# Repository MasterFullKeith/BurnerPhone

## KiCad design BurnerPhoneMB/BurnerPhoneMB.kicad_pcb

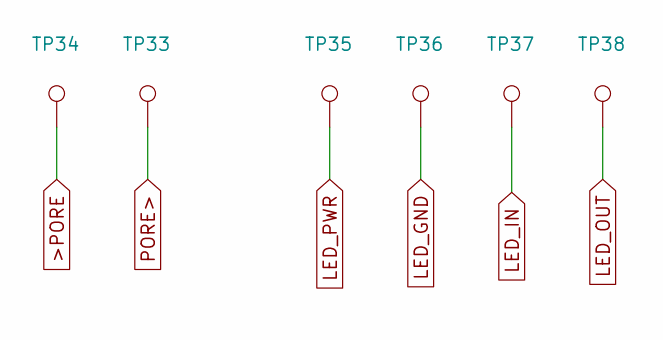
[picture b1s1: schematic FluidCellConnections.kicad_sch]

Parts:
TP33, TP34, TP35, TP36, TP37, TP38: TestPoint; Test Point

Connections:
>PORE: TP34.1; also elsewhere on the board
LED_GND: TP36.1
LED_IN: TP37.1
LED_OUT: TP38.1
LED_PWR: TP35.1
PORE>: TP33.1; also elsewhere on the board

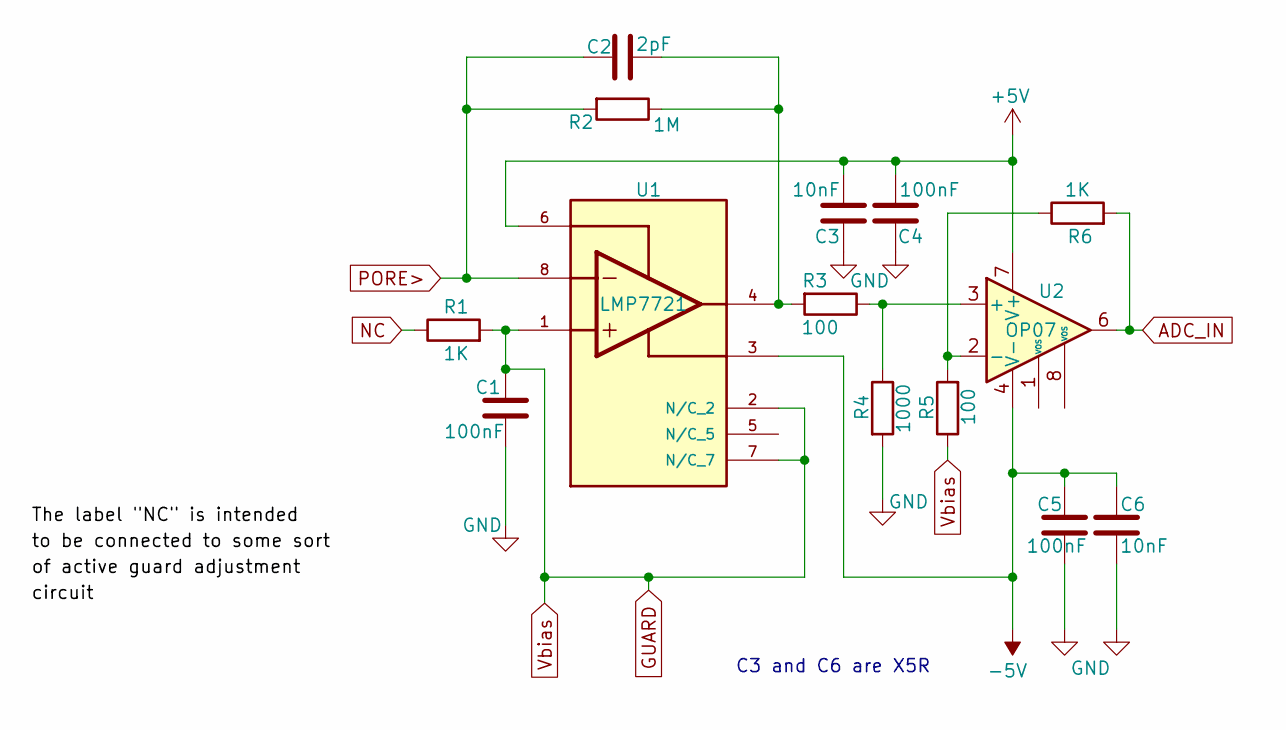
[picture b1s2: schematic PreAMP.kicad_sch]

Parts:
C1, C4, C5: 100nF; R_0805_2012Metric
C2: 2pF; R_0805_2012Metric
C3, C6: 10nF; R_0805_2012Metric
R1, R6: 1K; R_0805_2012Metric
R2: 1M; R_0805_2012Metric
R3, R5: 100; R_0805_2012Metric
R4: 1000; R_0805_2012Metric
U1: LMP7721; SOIC-8-1EP_3.9x4.9mm_P1.27mm_EP2.29x3mm; PARTREV E
U2: OP07; SOIC-8-1EP_3.9x4.9mm_P1.27mm_EP2.29x3mm

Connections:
+5V: C3.2, C4.2, U1.6, U2.7 (V+); also elsewhere on the board
-5V: C5.1, C6.1, U1.3, U2.4 (V-); also elsewhere on the board
ADC_IN: R6.2, U2.6; also elsewhere on the board
GND: C1.2, C3.1, C4.1, C5.2, C6.2, R4.2; also elsewhere on the board
GUARD: C1.1, R1.2, R5.1, U1.1, U1.2 (N/C), U1.7 (N/C)
NC: R1.1
unnamed: C2.1, R2.1, R3.2, U1.4
unnamed: R3.1, R4.1, U2.3 (+)
unnamed: R5.2, R6.1, U2.2 (-)
PORE>: C2.2, R2.2, U1.8; also elsewhere on the board

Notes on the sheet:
C3 and C6 are X5R

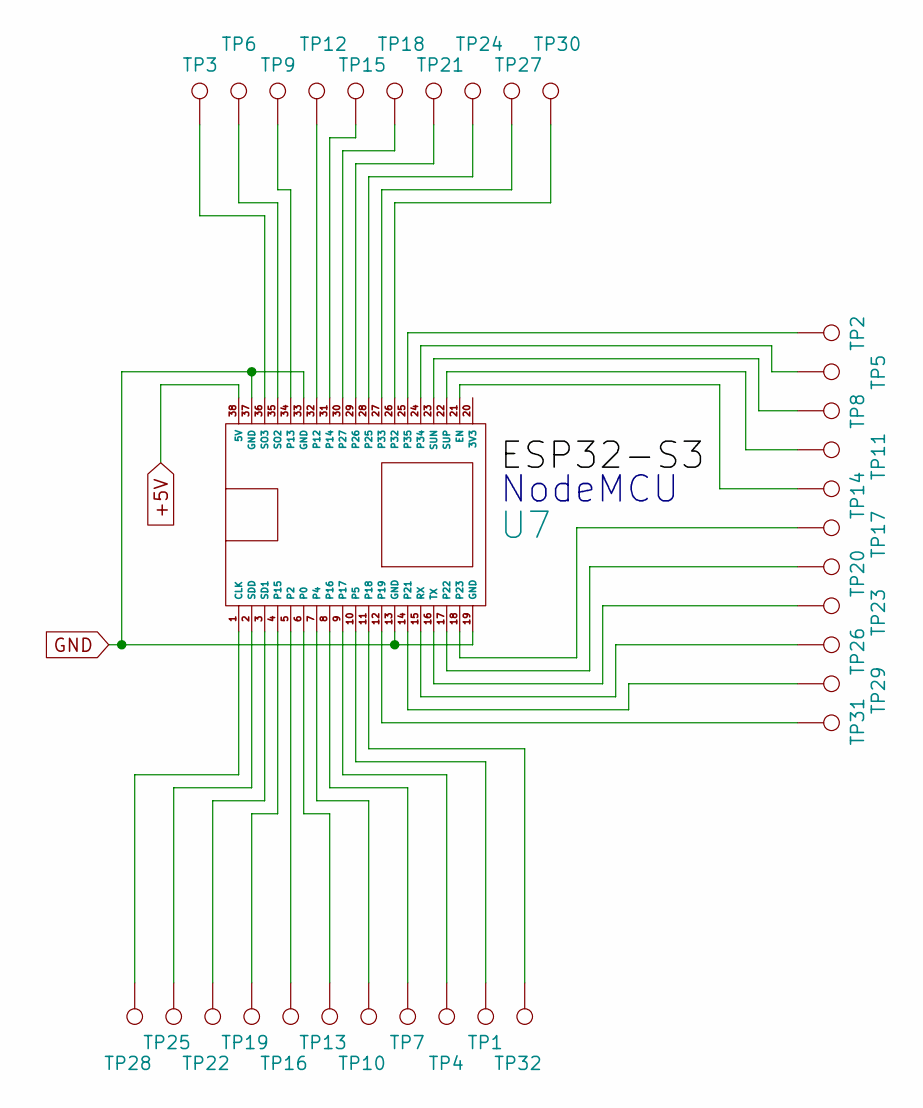
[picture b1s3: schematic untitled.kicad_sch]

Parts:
TP1, TP2, TP3, TP4, TP5, TP6, TP7, TP8, TP9, TP10, TP11, TP12, TP13, TP14, TP15, TP16, TP17, TP18, TP19, TP20, TP21, TP22, TP23, TP24, TP25, TP26, TP27, TP28, TP29, TP30, TP31, TP32: TestPoint; Test Point
U7: ESP32-19x19

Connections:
+5V: U7.38 (5V); also elsewhere on the board
GND: U7.13 (GND), U7.19 (GND), U7.33 (GND), U7.37 (GND); also elsewhere on the board
unnamed: TP28.1, U7.1 (CLK)
unnamed: TP14.1, U7.21 (EN)
unnamed: TP13.1, U7.6 (P0)
unnamed: TP16.1, U7.5 (P2)
unnamed: TP10.1, U7.7 (P4)
unnamed: TP1.1, U7.10 (P5)
unnamed: TP12.1, U7.32 (P12)
unnamed: TP9.1, U7.34 (P13)
unnamed: TP15.1, U7.31 (P14)
unnamed: TP19.1, U7.4 (P15)
unnamed: TP7.1, U7.8 (P16)
unnamed: TP4.1, U7.9 (P17)
unnamed: TP32.1, U7.11 (P18)
unnamed: TP31.1, U7.12 (P19)
unnamed: TP29.1, U7.14 (P21)
unnamed: TP20.1, U7.17 (P22)
unnamed: TP17.1, U7.18 (P23)
unnamed: TP24.1, U7.28 (P25)
unnamed: TP21.1, U7.29 (P26)
unnamed: TP18.1, U7.30 (P27)
unnamed: TP30.1, U7.26 (P32)
unnamed: TP27.1, U7.27 (P33)
unnamed: TP5.1, U7.24 (P34)
unnamed: TP2.1, U7.25 (P35)
unnamed: TP26.1, U7.15 (RX)
unnamed: TP22.1, U7.3 (SD1)
unnamed: TP25.1, U7.2 (SDD)
unnamed: TP6.1, U7.35 (SO2)
unnamed: TP3.1, U7.36 (SO3)
unnamed: TP8.1, U7.23 (SUN)
unnamed: TP11.1, U7.22 (SUP)
unnamed: TP23.1, U7.16 (TX)

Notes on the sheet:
NodeMCU

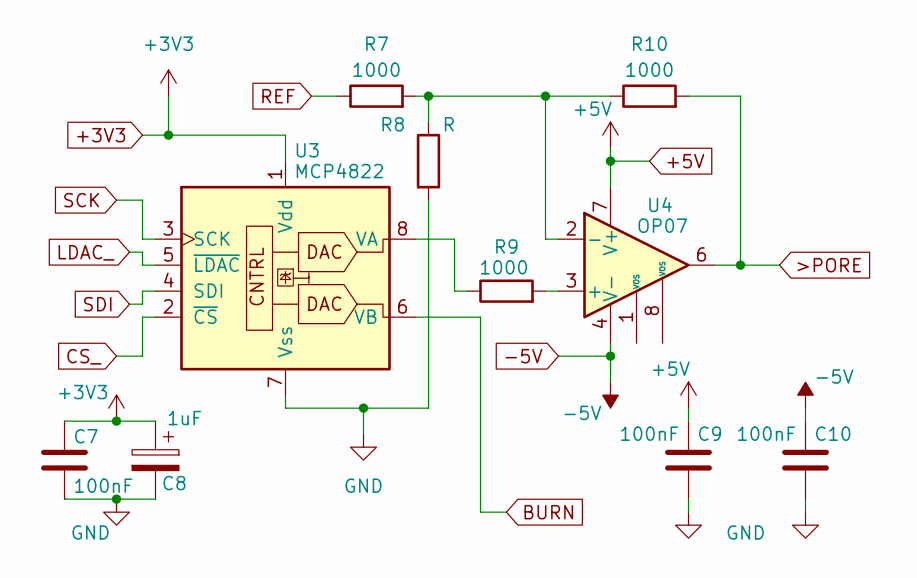
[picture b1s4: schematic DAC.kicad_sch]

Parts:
C7, C9, C10: 100nF; R_0805_2012Metric
C8: 1uF; R_0805_2012Metric
R7, R9, R10: 1000; R_0805_2012Metric
R8: R; R_0805_2012Metric
U3: MCP4822; SOIC-8-1EP_3.9x4.9mm_P1.27mm_EP2.29x3mm
U4: OP07; SOIC-8-1EP_3.9x4.9mm_P1.27mm_EP2.29x3mm

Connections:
+3V3: C7.1, C8.1, U3.1 (Vdd); also elsewhere on the board
+5V: C9.1, U4.7 (V+); also elsewhere on the board
-5V: C10.1, U4.4 (V-); also elsewhere on the board
>PORE: R10.2, U4.6; also elsewhere on the board
BURN: U3.6 (VB)
CS_: U3.2 (~CS)
GND: C7.2, C8.2, C9.2, C10.2, R8.2, U3.7 (Vss); also elsewhere on the board
LDAC_: U3.5 (~LDAC)
unnamed: R9.1, U3.8 (VA)
unnamed: R9.2, U4.3 (+)
unnamed: R7.2, R8.1, R10.1, U4.2 (-)
REF: R7.1
SCK: U3.3 (SCK)
SDI: U3.4 (SDI)

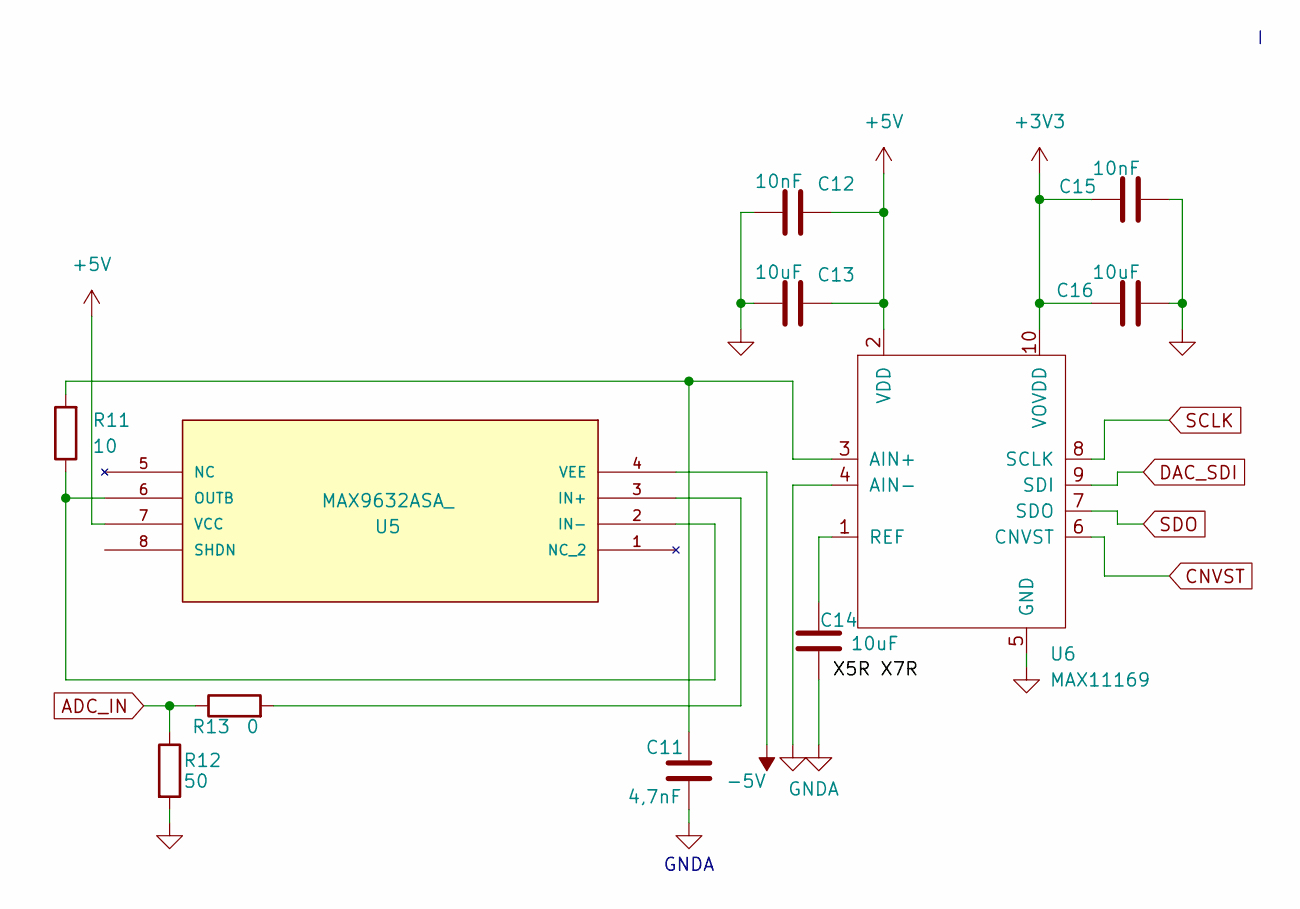
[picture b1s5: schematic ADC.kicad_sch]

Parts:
C11: 4,7nF; R_0805_2012Metric
C12, C15: 10nF; R_0805_2012Metric
C13, C16: 10uF; R_0805_2012Metric
C14: 10uF; R_1206_3216Metric
R11: 10; R_0805_2012Metric
R12: 50; R_0805_2012Metric
R13: 0; R_0805_2012Metric
U5: MAX9632ASA_; SOIC-8-1EP_3.9x4.9mm_P1.27mm_EP2.29x3mm; MANUFACTURER_PART_NUMBER max9632asa+t
U6: MAX11169; MSOP-10-1EP_3x3mm_P0.5mm_EP1.68x1.88mm

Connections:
+3V3: C15.2, C16.2, U6.10 (VOVDD); also elsewhere on the board
+5V: C12.1, C13.1, U5.7 (VCC), U6.2 (VDD); also elsewhere on the board
-5V: U5.4 (VEE); also elsewhere on the board
ADC_IN: R12.1, R13.1; also elsewhere on the board
CNVST: U6.6 (CNVST)
DAC_SDI: U6.9 (SDI)
GND: C12.2, C13.2, C15.1, C16.1, R12.2, U6.5 (GND); also elsewhere on the board
GNDA: C11.2, C14.2, U6.4 (AIN-)
unnamed: R13.2, U5.3 (IN+)
unnamed: R11.1, U5.2 (IN-), U5.6 (OUTB)
unnamed: C11.1, R11.2, U6.3 (AIN+)
unnamed: C14.1, U6.1 (REF)
SCLK: U6.8 (SCLK)
SDO: U6.7 (SDO)

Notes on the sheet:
GNDA

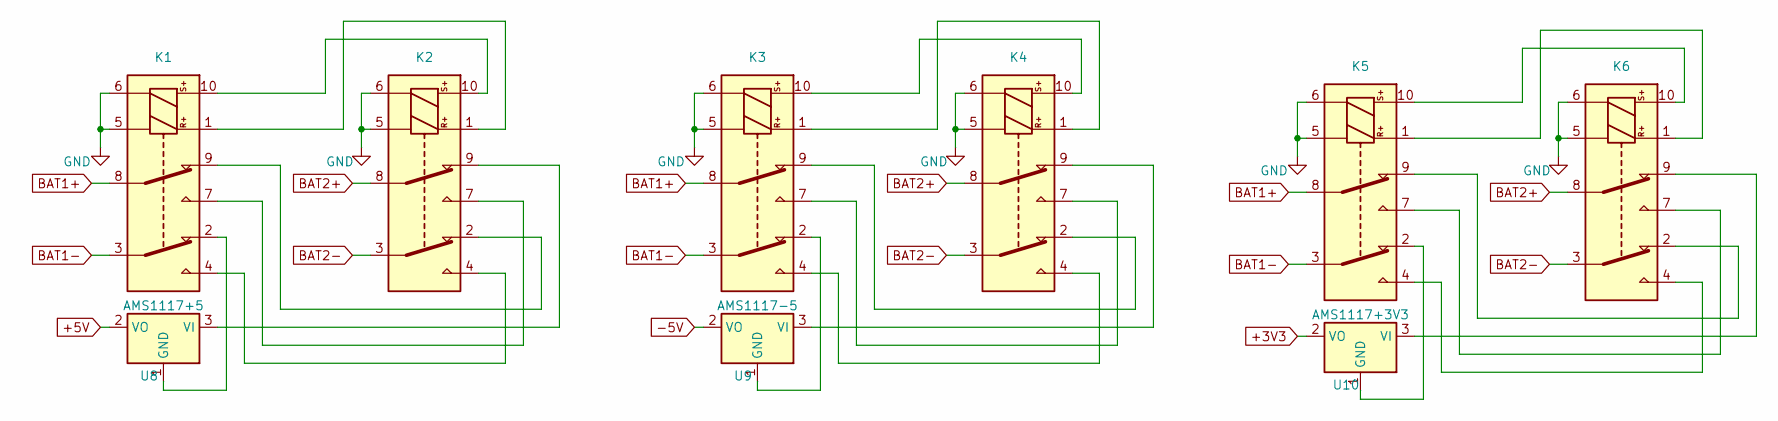
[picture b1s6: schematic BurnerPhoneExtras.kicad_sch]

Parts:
K1, K2, K3, K4, K5, K6: Relay_DPST_Latching_2coil; relay
U8: AMS1117+5; SOT-223-3_TabPin2
U9: AMS1117-5; SOT-223-3_TabPin2
U10: AMS1117+3V3; SOT-223-3_TabPin2

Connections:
+3V3: U10.2 (VO); also elsewhere on the board
+5V: U8.2 (VO); also elsewhere on the board
-5V: U9.2 (VO); also elsewhere on the board
BAT1+: K1.8, K3.8, K5.8
BAT1-: K1.3, K3.3, K5.3
BAT2+: K2.8, K4.8, K6.8
BAT2-: K2.3, K4.3, K6.3
GND: K1.5, K1.6, K2.5, K2.6, K3.5, K3.6, K4.5, K4.6, K5.5, K5.6, K6.5, K6.6; also elsewhere on the board
unnamed: K1.1, K2.1
unnamed: K1.4, K2.4
unnamed: K1.7, K2.7
unnamed: K1.9, K2.2
unnamed: K1.10, K2.10
unnamed: K3.1, K4.1
unnamed: K3.4, K4.4
unnamed: K3.7, K4.7
unnamed: K3.9, K4.2
unnamed: K3.10, K4.10
unnamed: K5.1, K6.1
unnamed: K5.4, K6.4
unnamed: K5.7, K6.7
unnamed: K5.9, K6.2
unnamed: K5.10, K6.10
unnamed: K1.2, U8.1 (GND)
unnamed: K2.9, U8.3 (VI)
unnamed: K3.2, U9.1 (GND)
unnamed: K4.9, U9.3 (VI)
unnamed: K5.2, U10.1 (GND)
unnamed: K6.9, U10.3 (VI)

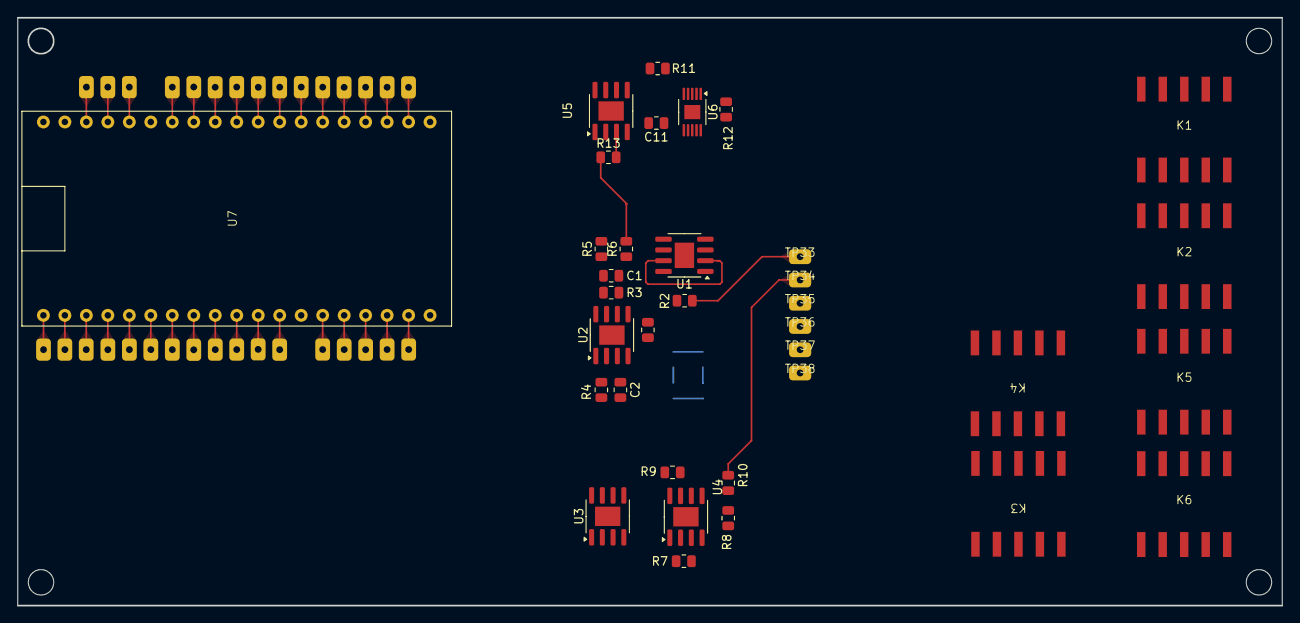
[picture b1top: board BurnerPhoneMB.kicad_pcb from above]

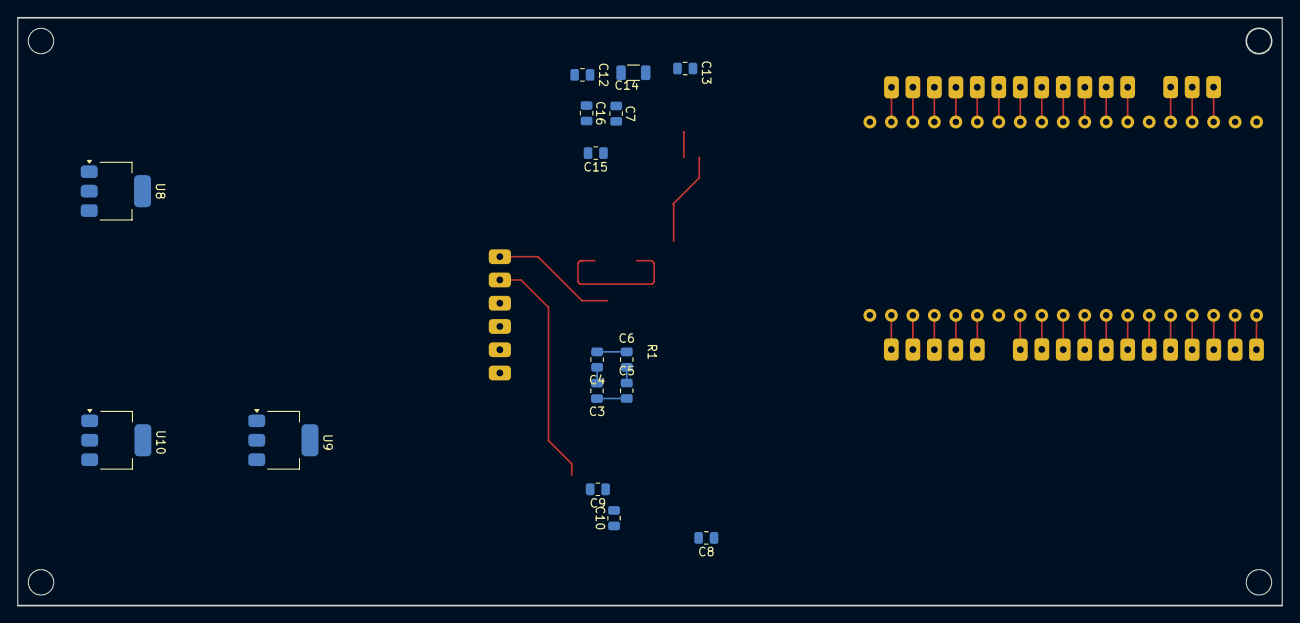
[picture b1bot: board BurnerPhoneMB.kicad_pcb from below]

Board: 4 copper layers, 149.5 x 69.5 mm, 83 parts (16 on the bottom side), 76 nets.
